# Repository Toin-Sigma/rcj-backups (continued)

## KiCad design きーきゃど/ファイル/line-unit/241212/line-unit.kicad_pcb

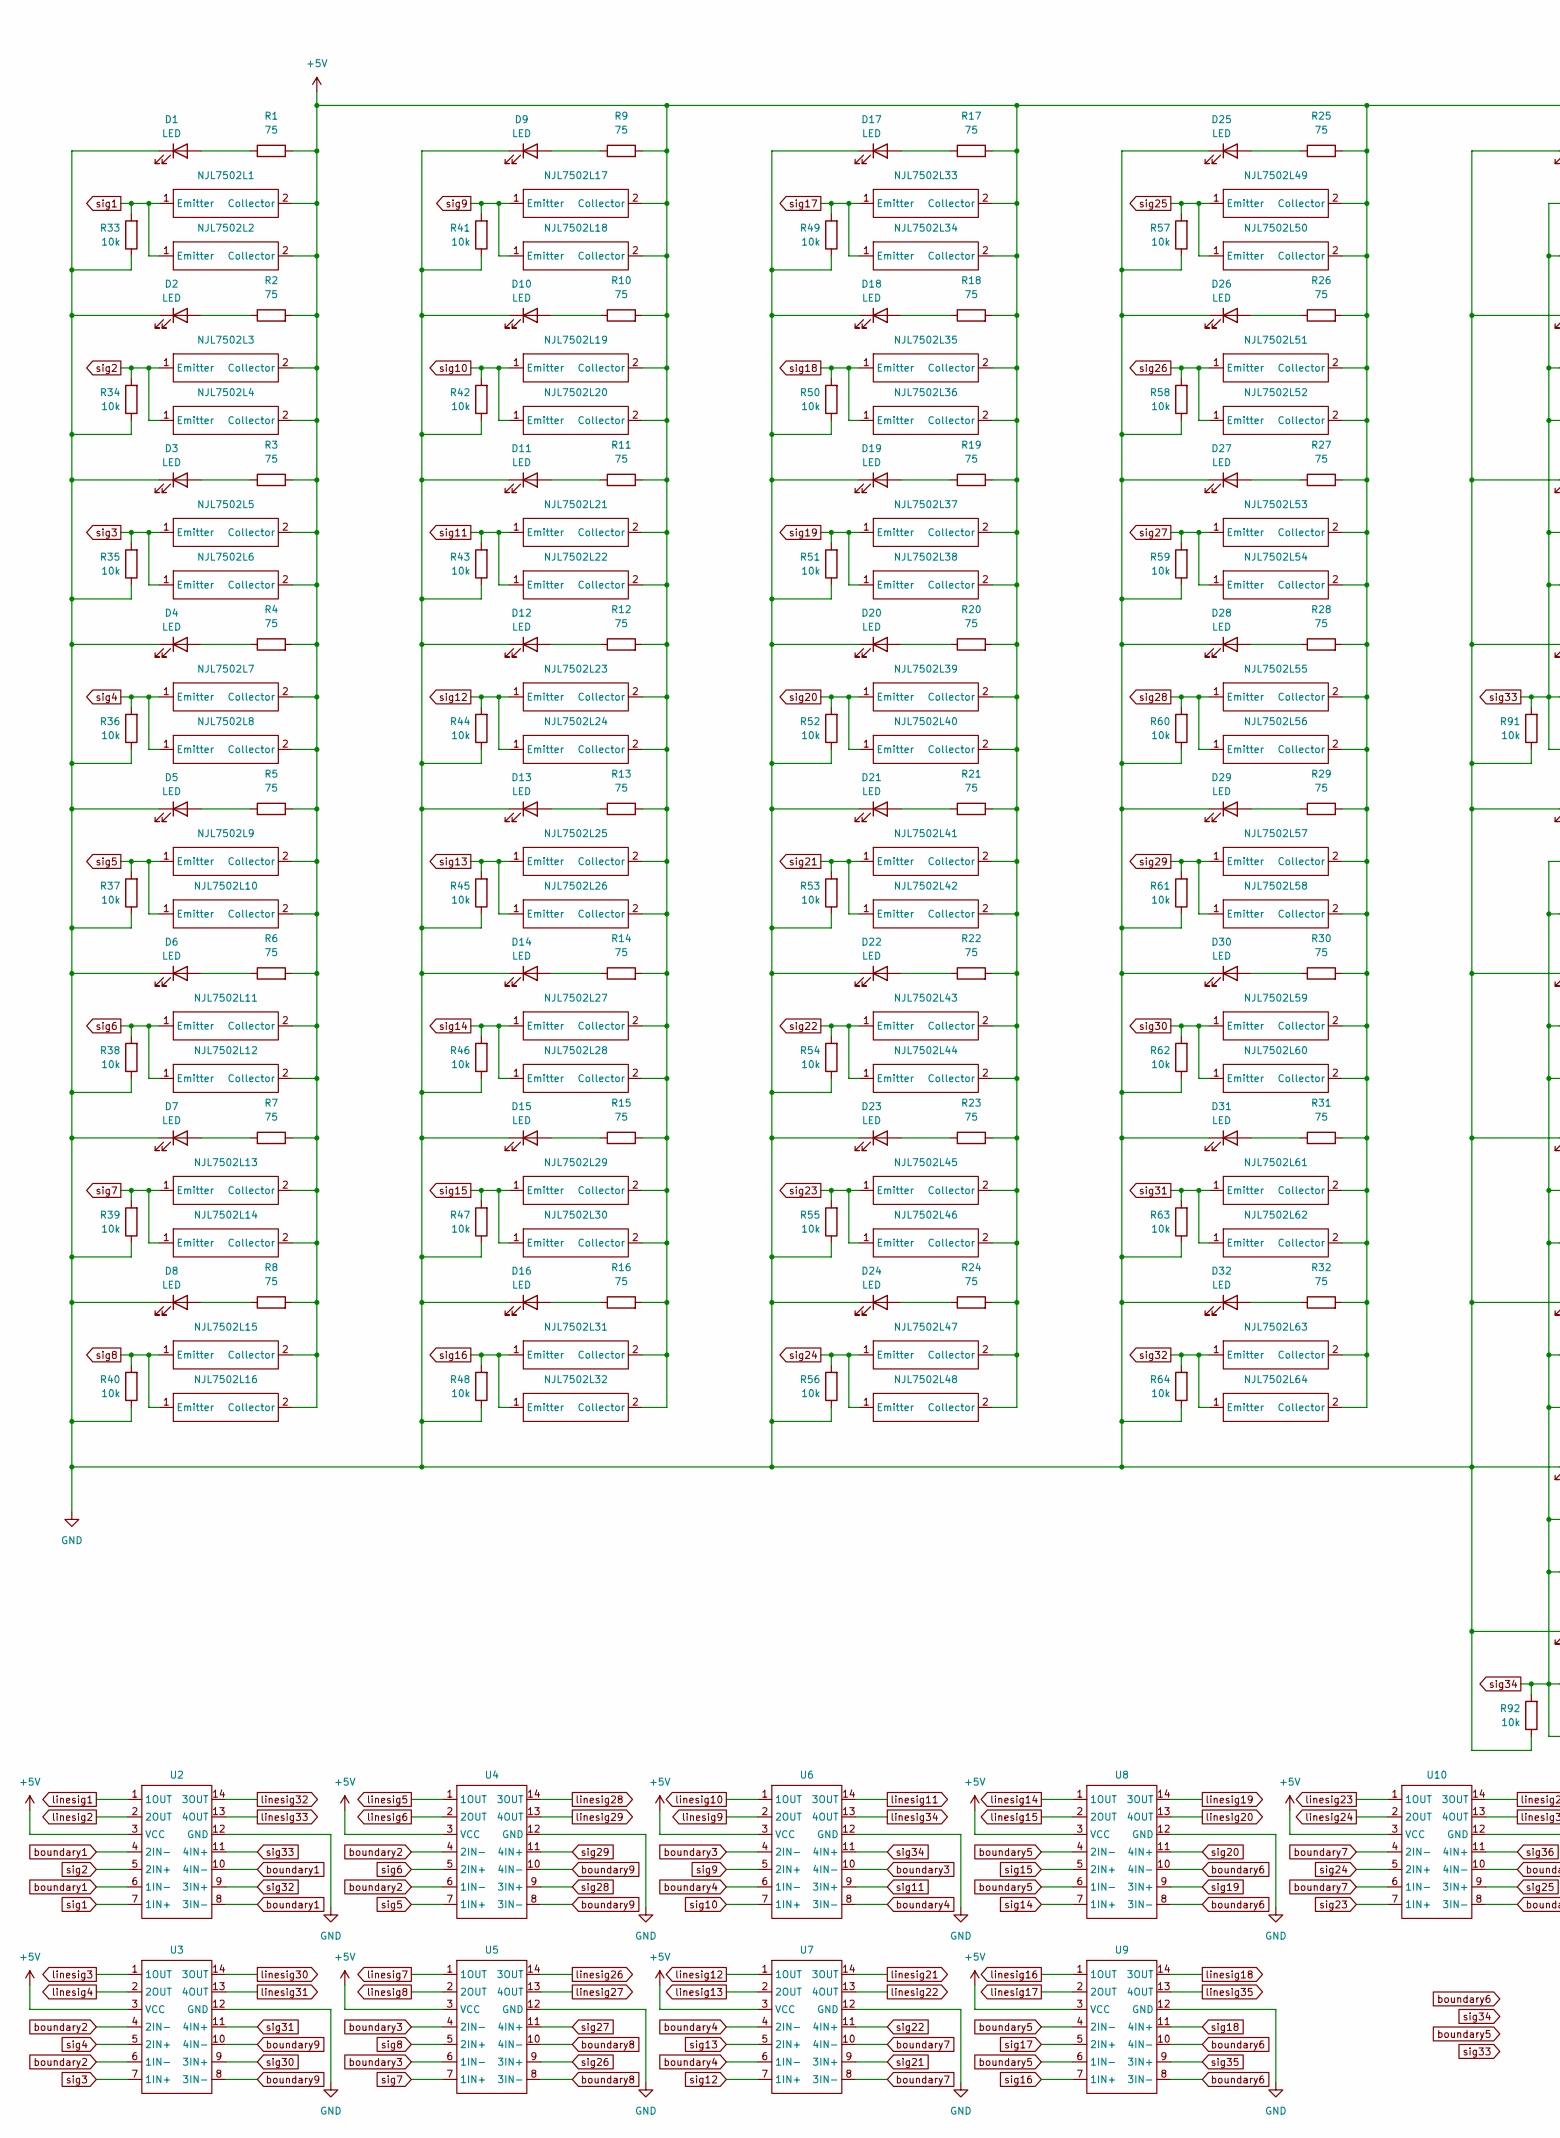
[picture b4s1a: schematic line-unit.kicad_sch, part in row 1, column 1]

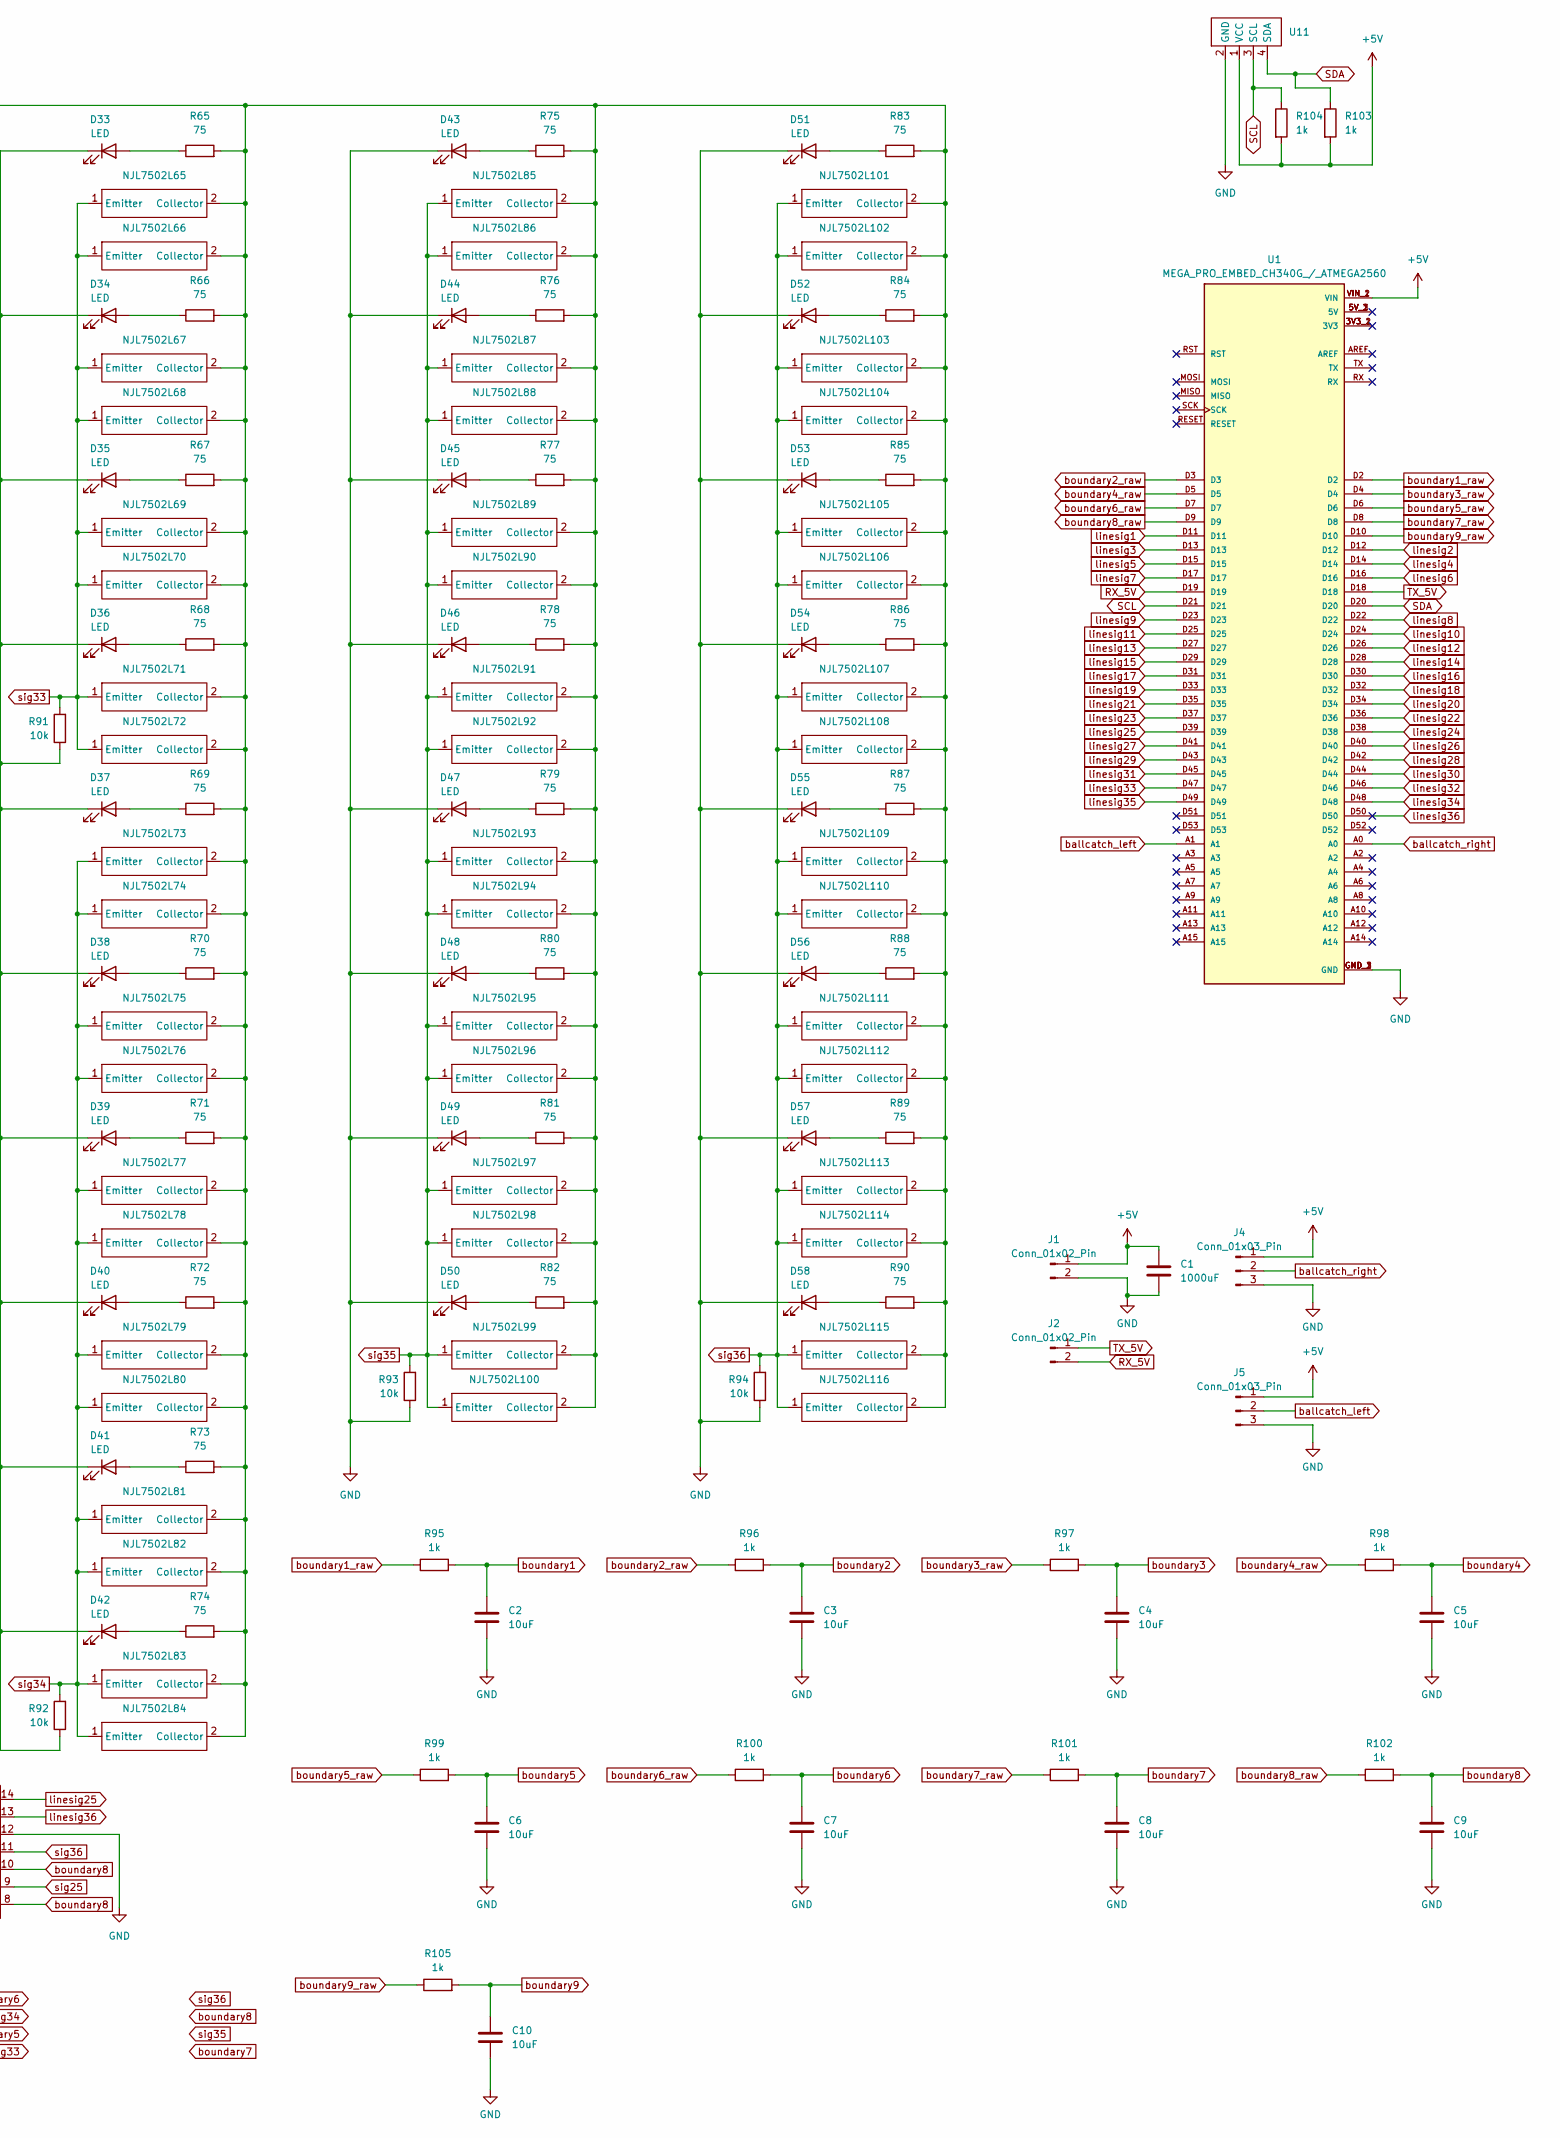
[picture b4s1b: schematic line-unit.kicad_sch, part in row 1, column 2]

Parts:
C1: 1000uF; CP_Radial_D12.5mm_P5.00mm
C2, C3, C4, C5, C6, C7, C8, C9, C10: 10uF; C-1206_3216-Handsolder
D1, D2, D3, D4, D5, D6, D7, D8, D9, D10, D11, D12, D13, D14, D15, D16, D17, D18, D19, D20, D21, D22, D23, D24, D25, D26, D27, D28, D29, D30, D31, D32, D33, D34, D35, D36, D37, D38, D39, D40, D41, D42, D43, D44, D45, D46, D47, D48, D49, D50, D51, D52, D53, D54, D55, D56, D57, D58: LED
J1: Conn_01x02_Pin; AMASS_XT30U-F_1x02_P5.0mm_Vertical
J2: Conn_01x02_Pin; JST_XH_B2B-XH-A_1x02_P2.50mm_Vertical
J4, J5: Conn_01x03_Pin; JST_XH_B3B-XH-A_1x03_P2.50mm_Vertical
NJL7502L1, NJL7502L2, NJL7502L3, NJL7502L4, NJL7502L5, NJL7502L6, NJL7502L7, NJL7502L8, NJL7502L9, NJL7502L10, NJL7502L11, NJL7502L12, NJL7502L13, NJL7502L14, NJL7502L15, NJL7502L16, NJL7502L17, NJL7502L18, NJL7502L19, NJL7502L20, NJL7502L21, NJL7502L22, NJL7502L23, NJL7502L24, NJL7502L25, NJL7502L26, NJL7502L27, NJL7502L28, NJL7502L29, NJL7502L30, NJL7502L31, NJL7502L32, NJL7502L33, NJL7502L34, NJL7502L35, NJL7502L36, NJL7502L37, NJL7502L38, NJL7502L39, NJL7502L40, NJL7502L41, NJL7502L42, NJL7502L43, NJL7502L44, NJL7502L45, NJL7502L46, NJL7502L47, NJL7502L48, NJL7502L49, NJL7502L50, NJL7502L51, NJL7502L52, NJL7502L53, NJL7502L54, NJL7502L55, NJL7502L56, NJL7502L57, NJL7502L58, NJL7502L59, NJL7502L60, NJL7502L61, NJL7502L62, NJL7502L63, NJL7502L64, NJL7502L65, NJL7502L66, NJL7502L67, NJL7502L68, NJL7502L69, NJL7502L70, NJL7502L71, NJL7502L72, NJL7502L73, NJL7502L74, NJL7502L75, NJL7502L76, NJL7502L77, NJL7502L78, NJL7502L79, NJL7502L80, NJL7502L81, NJL7502L82, NJL7502L83, NJL7502L84, NJL7502L85, NJL7502L86, NJL7502L87, NJL7502L88, NJL7502L89, NJL7502L90, NJL7502L91, NJL7502L92, NJL7502L93, NJL7502L94, NJL7502L95, NJL7502L96, NJL7502L97, NJL7502L98, NJL7502L99, NJL7502L100, NJL7502L101, NJL7502L102, NJL7502L103, NJL7502L104, NJL7502L105, NJL7502L106, NJL7502L107, NJL7502L108, NJL7502L109, NJL7502L110, NJL7502L111, NJL7502L112, NJL7502L113, NJL7502L114, NJL7502L115, NJL7502L116: NJL7502L
R1, R2, R3, R4, R5, R6, R7, R8, R9, R10, R11, R12, R13, R14, R15, R16, R17, R18, R19, R20, R21, R22, R23, R24, R25, R26, R27, R28, R29, R30, R31, R32, R65, R66, R67, R68, R69, R70, R71, R72, R73, R74, R75, R76, R77, R78, R79, R80, R81, R82, R83, R84, R85, R86, R87, R88, R89, R90: 75; R-1206_3216-Handsolder
R33, R34, R35, R36, R37, R38, R39, R40, R41, R42, R43, R44, R45, R46, R47, R48, R49, R50, R51, R52, R53, R54, R55, R56, R57, R58, R59, R60, R61, R62, R63, R64, R91, R92, R93, R94: 10k; R-1206_3216-Handsolder
R95, R96, R97, R98, R99, R100, R101, R102, R105: 1k; R-1206_3216-Handsolder
R103, R104: 1k
U1: MEGA_PRO_EMBED_CH340G_/_ATMEGA2560; MODULE_MEGA_PRO_EMBED_CH340G___ATMEGA2560
U2, U3, U4, U5, U6, U7, U8, U9, U10: LM339
U11: (no value)

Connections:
+5V: C1.1, J1.1, J4.1, J5.1, NJL7502L1.2 (Collector), NJL7502L2.2 (Collector), NJL7502L3.2 (Collector), NJL7502L4.2 (Collector), NJL7502L5.2 (Collector), NJL7502L6.2 (Collector), NJL7502L7.2 (Collector), NJL7502L8.2 (Collector), NJL7502L9.2 (Collector), NJL7502L10.2 (Collector), NJL7502L11.2 (Collector), NJL7502L12.2 (Collector), NJL7502L13.2 (Collector), NJL7502L14.2 (Collector), NJL7502L15.2 (Collector), NJL7502L16.2 (Collector), NJL7502L17.2 (Collector), NJL7502L18.2 (Collector), NJL7502L19.2 (Collector), NJL7502L20.2 (Collector), NJL7502L21.2 (Collector), NJL7502L22.2 (Collector), NJL7502L23.2 (Collector), NJL7502L24.2 (Collector), NJL7502L25.2 (Collector), NJL7502L26.2 (Collector), NJL7502L27.2 (Collector), NJL7502L28.2 (Collector), NJL7502L29.2 (Collector), NJL7502L30.2 (Collector), NJL7502L31.2 (Collector), NJL7502L32.2 (Collector), NJL7502L33.2 (Collector), NJL7502L34.2 (Collector), NJL7502L35.2 (Collector), NJL7502L36.2 (Collector), NJL7502L37.2 (Collector), NJL7502L38.2 (Collector), NJL7502L39.2 (Collector), NJL7502L40.2 (Collector), NJL7502L41.2 (Collector), NJL7502L42.2 (Collector), NJL7502L43.2 (Collector), NJL7502L44.2 (Collector), NJL7502L45.2 (Collector), NJL7502L46.2 (Collector), NJL7502L47.2 (Collector), NJL7502L48.2 (Collector), NJL7502L49.2 (Collector), NJL7502L50.2 (Collector), NJL7502L51.2 (Collector), NJL7502L52.2 (Collector), NJL7502L53.2 (Collector), NJL7502L54.2 (Collector), NJL7502L55.2 (Collector), NJL7502L56.2 (Collector), NJL7502L57.2 (Collector), NJL7502L58.2 (Collector), NJL7502L59.2 (Collector), NJL7502L60.2 (Collector), NJL7502L61.2 (Collector), NJL7502L62.2 (Collector), NJL7502L63.2 (Collector), NJL7502L64.2 (Collector), NJL7502L65.2 (Collector), NJL7502L66.2 (Collector), NJL7502L67.2 (Collector), NJL7502L68.2 (Collector), NJL7502L69.2 (Collector), NJL7502L70.2 (Collector), NJL7502L71.2 (Collector), NJL7502L72.2 (Collector), NJL7502L73.2 (Collector), NJL7502L74.2 (Collector), NJL7502L75.2 (Collector), NJL7502L76.2 (Collector), NJL7502L77.2 (Collector), NJL7502L78.2 (Collector), NJL7502L79.2 (Collector), NJL7502L80.2 (Collector), NJL7502L81.2 (Collector), NJL7502L82.2 (Collector), NJL7502L83.2 (Collector), NJL7502L84.2 (Collector), NJL7502L85.2 (Collector), NJL7502L86.2 (Collector), NJL7502L87.2 (Collector), NJL7502L88.2 (Collector), NJL7502L89.2 (Collector), NJL7502L90.2 (Collector), NJL7502L91.2 (Collector), NJL7502L92.2 (Collector), NJL7502L93.2 (Collector), NJL7502L94.2 (Collector), NJL7502L95.2 (Collector), NJL7502L96.2 (Collector), NJL7502L97.2 (Collector), NJL7502L98.2 (Collector), NJL7502L99.2 (Collector), NJL7502L100.2 (Collector), NJL7502L101.2 (Collector), NJL7502L102.2 (Collector), NJL7502L103.2 (Collector), NJL7502L104.2 (Collector), NJL7502L105.2 (Collector), NJL7502L106.2 (Collector), NJL7502L107.2 (Collector), NJL7502L108.2 (Collector), NJL7502L109.2 (Collector), NJL7502L110.2 (Collector), NJL7502L111.2 (Collector), NJL7502L112.2 (Collector), NJL7502L113.2 (Collector), NJL7502L114.2 (Collector), NJL7502L115.2 (Collector), NJL7502L116.2 (Collector), R1.2, R2.2, R3.2, R4.2, R5.2, R6.2, R7.2, R8.2, R9.2, R10.2, R11.2, R12.2, R13.2, R14.2, R15.2, R16.2, R17.2, R18.2, R19.2, R20.2, R21.2, R22.2, R23.2, R24.2, R25.2, R26.2, R27.2, R28.2, R29.2, R30.2, R31.2, R32.2, R65.2, R66.2, R67.2, R68.2, R69.2, R70.2, R71.2, R72.2, R73.2, R74.2, R75.2, R76.2, R77.2, R78.2, R79.2, R80.2, R81.2, R82.2, R83.2, R84.2, R85.2, R86.2, R87.2, R88.2, R89.2, R90.2, R103.2, R104.2, U1.VIN_1 (VIN), U1.VIN_2 (VIN), U2.3 (VCC), U3.3 (VCC), U4.3 (VCC), U5.3 (VCC), U6.3 (VCC), U7.3 (VCC), U8.3 (VCC), U9.3 (VCC), U10.3 (VCC), U11.1 (VCC)
GND: C1.2, C2.2, C3.2, C4.2, C5.2, C6.2, C7.2, C8.2, C9.2, C10.2, D1.1 (K), D2.1 (K), D3.1 (K), D4.1 (K), D5.1 (K), D6.1 (K), D7.1 (K), D8.1 (K), D9.1 (K), D10.1 (K), D11.1 (K), D12.1 (K), D13.1 (K), D14.1 (K), D15.1 (K), D16.1 (K), D17.1 (K), D18.1 (K), D19.1 (K), D20.1 (K), D21.1 (K), D22.1 (K), D23.1 (K), D24.1 (K), D25.1 (K), D26.1 (K), D27.1 (K), D28.1 (K), D29.1 (K), D30.1 (K), D31.1 (K), D32.1 (K), D33.1 (K), D34.1 (K), D35.1 (K), D36.1 (K), D37.1 (K), D38.1 (K), D39.1 (K), D40.1 (K), D41.1 (K), D42.1 (K), D43.1 (K), D44.1 (K), D45.1 (K), D46.1 (K), D47.1 (K), D48.1 (K), D49.1 (K), D50.1 (K), D51.1 (K), D52.1 (K), D53.1 (K), D54.1 (K), D55.1 (K), D56.1 (K), D57.1 (K), D58.1 (K), J1.2, J4.3, J5.3, R33.1, R34.1, R35.1, R36.1, R37.1, R38.1, R39.1, R40.1, R41.1, R42.1, R43.1, R44.1, R45.1, R46.1, R47.1, R48.1, R49.1, R50.1, R51.1, R52.1, R53.1, R54.1, R55.1, R56.1, R57.1, R58.1, R59.1, R60.1, R61.1, R62.1, R63.1, R64.1, R91.1, R92.1, R93.1, R94.1, U1.GND_1 (GND), U1.GND_2 (GND), U1.GND_3 (GND), U2.12 (GND), U3.12 (GND), U4.12 (GND), U5.12 (GND), U6.12 (GND), U7.12 (GND), U8.12 (GND), U9.12 (GND), U10.12 (GND), U11.2 (GND)
unnamed: D1.2 (A), R1.1
unnamed: D2.2 (A), R2.1
unnamed: D3.2 (A), R3.1
unnamed: D4.2 (A), R4.1
unnamed: D5.2 (A), R5.1
unnamed: D6.2 (A), R6.1
unnamed: D7.2 (A), R7.1
unnamed: D8.2 (A), R8.1
unnamed: D9.2 (A), R9.1
unnamed: D10.2 (A), R10.1
unnamed: D11.2 (A), R11.1
unnamed: D12.2 (A), R12.1
unnamed: D13.2 (A), R13.1
unnamed: D14.2 (A), R14.1
unnamed: D15.2 (A), R15.1
unnamed: D16.2 (A), R16.1
unnamed: D17.2 (A), R17.1
unnamed: D18.2 (A), R18.1
unnamed: D19.2 (A), R19.1
unnamed: D20.2 (A), R20.1
unnamed: D21.2 (A), R21.1
unnamed: D22.2 (A), R22.1
unnamed: D23.2 (A), R23.1
unnamed: D24.2 (A), R24.1
unnamed: D25.2 (A), R25.1
unnamed: D26.2 (A), R26.1
unnamed: D27.2 (A), R27.1
unnamed: D28.2 (A), R28.1
unnamed: D29.2 (A), R29.1
unnamed: D30.2 (A), R30.1
unnamed: D31.2 (A), R31.1
unnamed: D32.2 (A), R32.1
unnamed: D33.2 (A), R65.1
unnamed: D34.2 (A), R66.1
unnamed: D35.2 (A), R67.1
unnamed: D36.2 (A), R68.1
unnamed: D37.2 (A), R69.1
unnamed: D38.2 (A), R70.1
unnamed: D39.2 (A), R71.1
unnamed: D40.2 (A), R72.1
unnamed: D41.2 (A), R73.1
unnamed: D42.2 (A), R74.1
unnamed: D43.2 (A), R75.1
unnamed: D44.2 (A), R76.1
unnamed: D45.2 (A), R77.1
unnamed: D46.2 (A), R78.1
unnamed: D47.2 (A), R79.1
unnamed: D48.2 (A), R80.1
unnamed: D49.2 (A), R81.1
unnamed: D50.2 (A), R82.1
unnamed: D51.2 (A), R83.1
unnamed: D52.2 (A), R84.1
unnamed: D53.2 (A), R85.1
unnamed: D54.2 (A), R86.1
unnamed: D55.2 (A), R87.1
unnamed: D56.2 (A), R88.1
unnamed: D57.2 (A), R89.1
unnamed: D58.2 (A), R90.1
RX_5V: J2.2, U1.D19
SCL: R104.1, U1.D21, U11.3 (SCL)
SDA: R103.1, U1.D20, U11.4 (SDA)
TX_5V: J2.1, U1.D18
ballcatch_left: J5.2, U1.A1
ballcatch_right: J4.2, U1.A0
boundary1: C2.1, R95.2, U2.4 (2IN-), U2.6 (1IN-), U2.8 (3IN-), U2.10 (4IN-)
boundary1_raw: R95.1, U1.D2
boundary2: C3.1, R96.2, U3.4 (2IN-), U3.6 (1IN-), U4.4 (2IN-), U4.6 (1IN-)
boundary2_raw: R96.1, U1.D3
boundary3: C4.1, R97.2, U5.4 (2IN-), U5.6 (1IN-), U6.4 (2IN-), U6.10 (4IN-)
boundary3_raw: R97.1, U1.D4
boundary4: C5.1, R98.2, U6.6 (1IN-), U6.8 (3IN-), U7.4 (2IN-), U7.6 (1IN-)
boundary4_raw: R98.1, U1.D5
boundary5: C6.1, R99.2, U8.4 (2IN-), U8.6 (1IN-), U9.4 (2IN-), U9.6 (1IN-)
boundary5_raw: R99.1, U1.D6
boundary6: C7.1, R100.2, U8.8 (3IN-), U8.10 (4IN-), U9.8 (3IN-), U9.10 (4IN-)
boundary6_raw: R100.1, U1.D7
boundary7: C8.1, R101.2, U7.8 (3IN-), U7.10 (4IN-), U10.4 (2IN-), U10.6 (1IN-)
boundary7_raw: R101.1, U1.D8
boundary8: C9.1, R102.2, U5.8 (3IN-), U5.10 (4IN-), U10.8 (3IN-), U10.10 (4IN-)
boundary8_raw: R102.1, U1.D9
boundary9: C10.1, R105.2, U3.8 (3IN-), U3.10 (4IN-), U4.8 (3IN-), U4.10 (4IN-)
boundary9_raw: R105.1, U1.D10
linesig1: U1.D11, U2.1 (1OUT)
linesig2: U1.D12, U2.2 (2OUT)
linesig3: U1.D13, U3.1 (1OUT)
linesig4: U1.D14, U3.2 (2OUT)
linesig5: U1.D15, U4.1 (1OUT)
linesig6: U1.D16, U4.2 (2OUT)
linesig7: U1.D17, U5.1 (1OUT)
linesig8: U1.D22, U5.2 (2OUT)
linesig9: U1.D23, U6.2 (2OUT)
linesig10: U1.D24, U6.1 (1OUT)
linesig11: U1.D25, U6.14 (3OUT)
linesig12: U1.D26, U7.1 (1OUT)
linesig13: U1.D27, U7.2 (2OUT)
linesig14: U1.D28, U8.1 (1OUT)
linesig15: U1.D29, U8.2 (2OUT)
linesig16: U1.D30, U9.1 (1OUT)
linesig17: U1.D31, U9.2 (2OUT)
linesig18: U1.D32, U9.14 (3OUT)
linesig19: U1.D33, U8.14 (3OUT)
linesig20: U1.D34, U8.13 (4OUT)
linesig21: U1.D35, U7.14 (3OUT)
linesig22: U1.D36, U7.13 (4OUT)
linesig23: U1.D37, U10.1 (1OUT)
linesig24: U1.D38, U10.2 (2OUT)
linesig25: U1.D39, U10.14 (3OUT)
linesig26: U1.D40, U5.14 (3OUT)
linesig27: U1.D41, U5.13 (4OUT)
linesig28: U1.D42, U4.14 (3OUT)
linesig29: U1.D43, U4.13 (4OUT)
linesig30: U1.D44, U3.14 (3OUT)
linesig31: U1.D45, U3.13 (4OUT)
linesig32: U1.D46, U2.14 (3OUT)
linesig33: U1.D47, U2.13 (4OUT)
linesig34: U1.D48, U6.13 (4OUT)
linesig35: U1.D49, U9.13 (4OUT)
linesig36: U1.D50, U10.13 (4OUT)
sig1: NJL7502L1.1 (Emitter), NJL7502L2.1 (Emitter), R33.2, U2.7 (1IN+)
sig2: NJL7502L3.1 (Emitter), NJL7502L4.1 (Emitter), R34.2, U2.5 (2IN+)
sig3: NJL7502L5.1 (Emitter), NJL7502L6.1 (Emitter), R35.2, U3.7 (1IN+)
sig4: NJL7502L7.1 (Emitter), NJL7502L8.1 (Emitter), R36.2, U3.5 (2IN+)
sig5: NJL7502L9.1 (Emitter), NJL7502L10.1 (Emitter), R37.2, U4.7 (1IN+)
sig6: NJL7502L11.1 (Emitter), NJL7502L12.1 (Emitter), R38.2, U4.5 (2IN+)
sig7: NJL7502L13.1 (Emitter), NJL7502L14.1 (Emitter), R39.2, U5.7 (1IN+)
sig8: NJL7502L15.1 (Emitter), NJL7502L16.1 (Emitter), R40.2, U5.5 (2IN+)
sig9: NJL7502L17.1 (Emitter), NJL7502L18.1 (Emitter), R41.2, U6.5 (2IN+)
sig10: NJL7502L19.1 (Emitter), NJL7502L20.1 (Emitter), R42.2, U6.7 (1IN+)
sig11: NJL7502L21.1 (Emitter), NJL7502L22.1 (Emitter), R43.2, U6.9 (3IN+)
sig12: NJL7502L23.1 (Emitter), NJL7502L24.1 (Emitter), R44.2, U7.7 (1IN+)
sig13: NJL7502L25.1 (Emitter), NJL7502L26.1 (Emitter), R45.2, U7.5 (2IN+)
sig14: NJL7502L27.1 (Emitter), NJL7502L28.1 (Emitter), R46.2, U8.7 (1IN+)
sig15: NJL7502L29.1 (Emitter), NJL7502L30.1 (Emitter), R47.2, U8.5 (2IN+)
sig16: NJL7502L31.1 (Emitter), NJL7502L32.1 (Emitter), R48.2, U9.7 (1IN+)
sig17: NJL7502L33.1 (Emitter), NJL7502L34.1 (Emitter), R49.2, U9.5 (2IN+)
sig18: NJL7502L35.1 (Emitter), NJL7502L36.1 (Emitter), R50.2, U9.11 (4IN+)
sig19: NJL7502L37.1 (Emitter), NJL7502L38.1 (Emitter), R51.2, U8.9 (3IN+)
sig20: NJL7502L39.1 (Emitter), NJL7502L40.1 (Emitter), R52.2, U8.11 (4IN+)
sig21: NJL7502L41.1 (Emitter), NJL7502L42.1 (Emitter), R53.2, U7.9 (3IN+)
sig22: NJL7502L43.1 (Emitter), NJL7502L44.1 (Emitter), R54.2, U7.11 (4IN+)
sig23: NJL7502L45.1 (Emitter), NJL7502L46.1 (Emitter), R55.2, U10.7 (1IN+)
sig24: NJL7502L47.1 (Emitter), NJL7502L48.1 (Emitter), R56.2, U10.5 (2IN+)
sig25: NJL7502L49.1 (Emitter), NJL7502L50.1 (Emitter), R57.2, U10.9 (3IN+)
sig26: NJL7502L51.1 (Emitter), NJL7502L52.1 (Emitter), R58.2, U5.9 (3IN+)
sig27: NJL7502L53.1 (Emitter), NJL7502L54.1 (Emitter), R59.2, U5.11 (4IN+)
sig28: NJL7502L55.1 (Emitter), NJL7502L56.1 (Emitter), R60.2, U4.9 (3IN+)
sig29: NJL7502L57.1 (Emitter), NJL7502L58.1 (Emitter), R61.2, U4.11 (4IN+)
sig30: NJL7502L59.1 (Emitter), NJL7502L60.1 (Emitter), R62.2, U3.9 (3IN+)
sig31: NJL7502L61.1 (Emitter), NJL7502L62.1 (Emitter), R63.2, U3.11 (4IN+)
sig32: NJL7502L63.1 (Emitter), NJL7502L64.1 (Emitter), R64.2, U2.9 (3IN+)
sig33: NJL7502L65.1 (Emitter), NJL7502L66.1 (Emitter), NJL7502L67.1 (Emitter), NJL7502L68.1 (Emitter), NJL7502L69.1 (Emitter), NJL7502L70.1 (Emitter), NJL7502L71.1 (Emitter), NJL7502L72.1 (Emitter), R91.2, U2.11 (4IN+)
sig34: NJL7502L73.1 (Emitter), NJL7502L74.1 (Emitter), NJL7502L75.1 (Emitter), NJL7502L76.1 (Emitter), NJL7502L77.1 (Emitter), NJL7502L78.1 (Emitter), NJL7502L79.1 (Emitter), NJL7502L80.1 (Emitter), NJL7502L81.1 (Emitter), NJL7502L82.1 (Emitter), NJL7502L83.1 (Emitter), NJL7502L84.1 (Emitter), R92.2, U6.11 (4IN+)
sig35: NJL7502L85.1 (Emitter), NJL7502L86.1 (Emitter), NJL7502L87.1 (Emitter), NJL7502L88.1 (Emitter), NJL7502L89.1 (Emitter), NJL7502L90.1 (Emitter), NJL7502L91.1 (Emitter), NJL7502L92.1 (Emitter), NJL7502L93.1 (Emitter), NJL7502L94.1 (Emitter), NJL7502L95.1 (Emitter), NJL7502L96.1 (Emitter), NJL7502L97.1 (Emitter), NJL7502L98.1 (Emitter), NJL7502L99.1 (Emitter), NJL7502L100.1 (Emitter), R93.2, U9.9 (3IN+)
sig36: NJL7502L101.1 (Emitter), NJL7502L102.1 (Emitter), NJL7502L103.1 (Emitter), NJL7502L104.1 (Emitter), NJL7502L105.1 (Emitter), NJL7502L106.1 (Emitter), NJL7502L107.1 (Emitter), NJL7502L108.1 (Emitter), NJL7502L109.1 (Emitter), NJL7502L110.1 (Emitter), NJL7502L111.1 (Emitter), NJL7502L112.1 (Emitter), NJL7502L113.1 (Emitter), NJL7502L114.1 (Emitter), NJL7502L115.1 (Emitter), NJL7502L116.1 (Emitter), R94.2, U10.11 (4IN+)

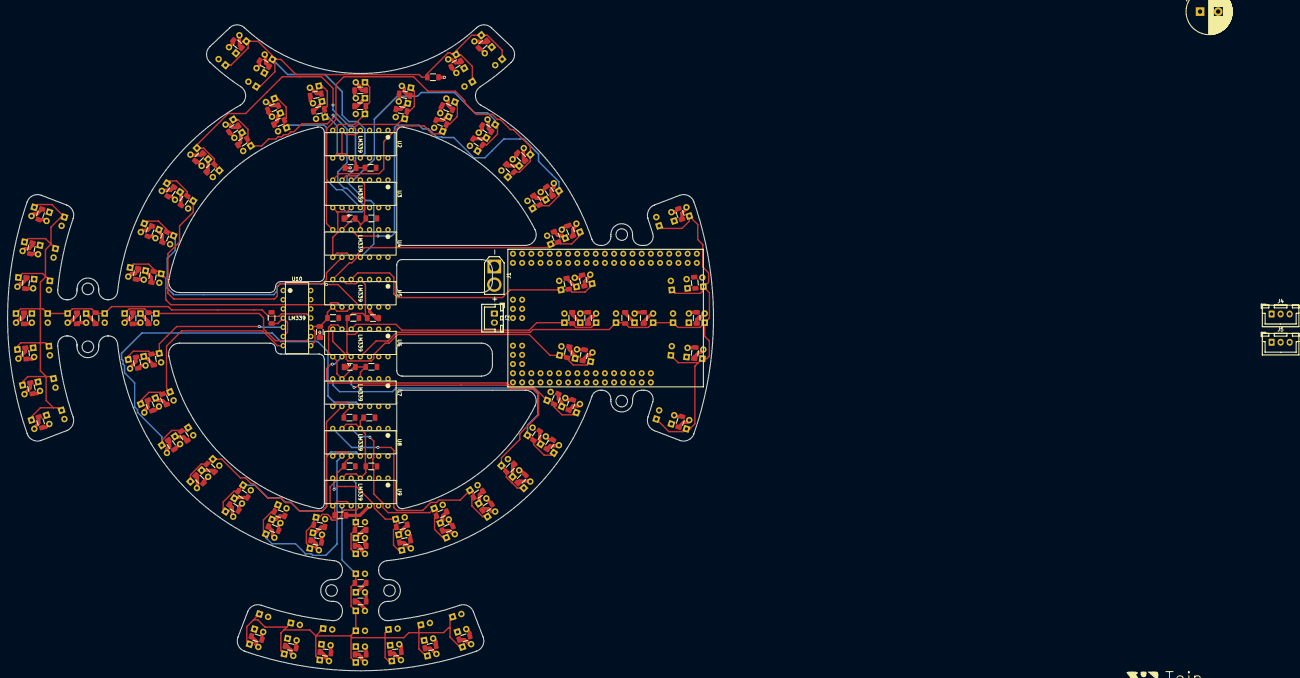
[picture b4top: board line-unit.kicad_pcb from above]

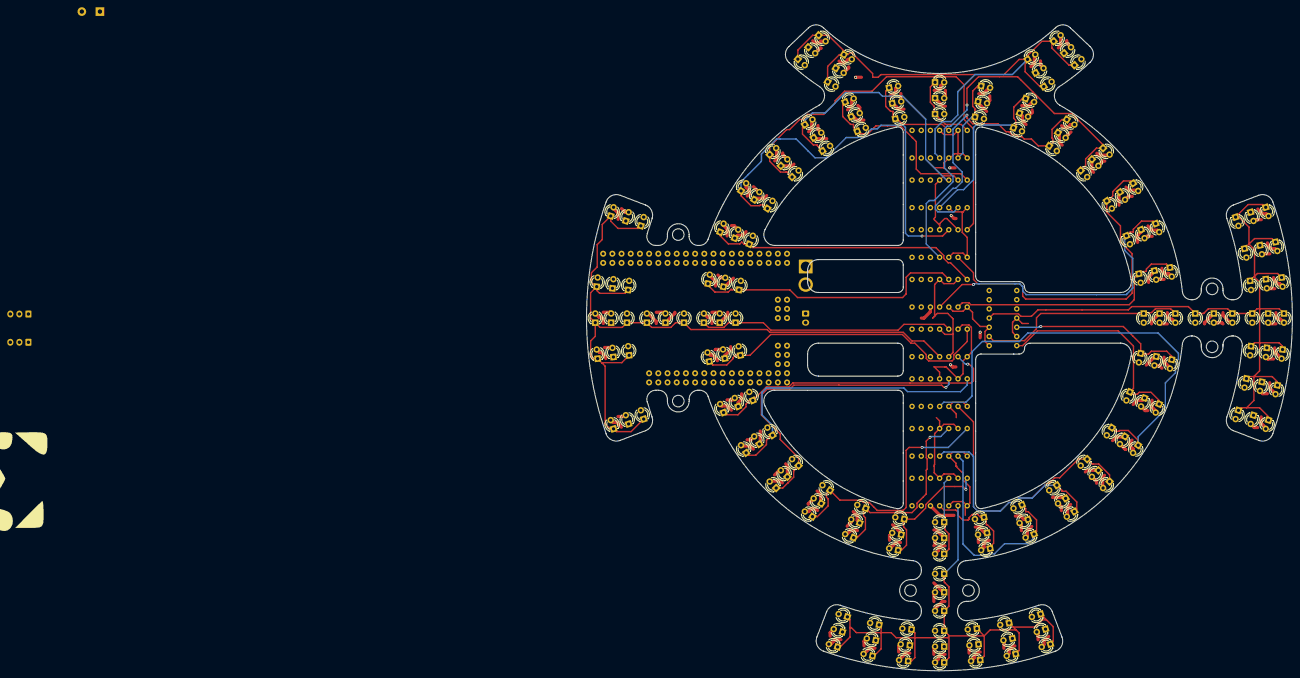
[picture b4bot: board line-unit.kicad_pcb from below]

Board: 4 copper layers, 195.0 x 178.4 mm, 299 parts (174 on the bottom side), 153 nets.

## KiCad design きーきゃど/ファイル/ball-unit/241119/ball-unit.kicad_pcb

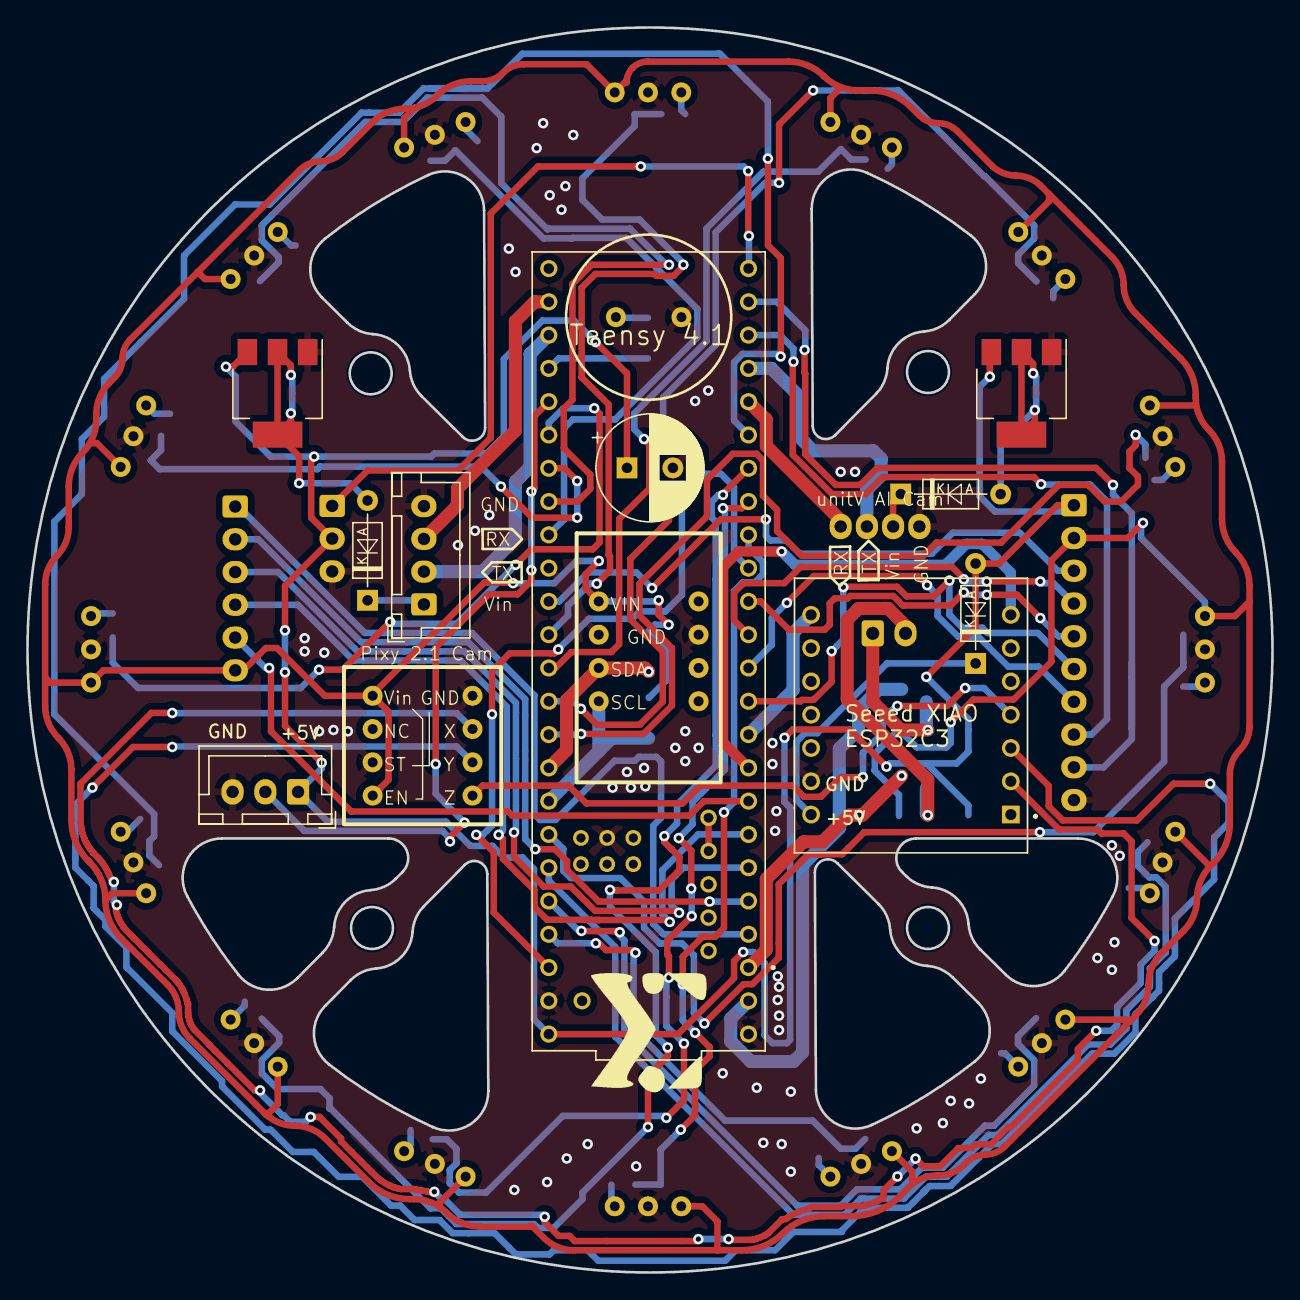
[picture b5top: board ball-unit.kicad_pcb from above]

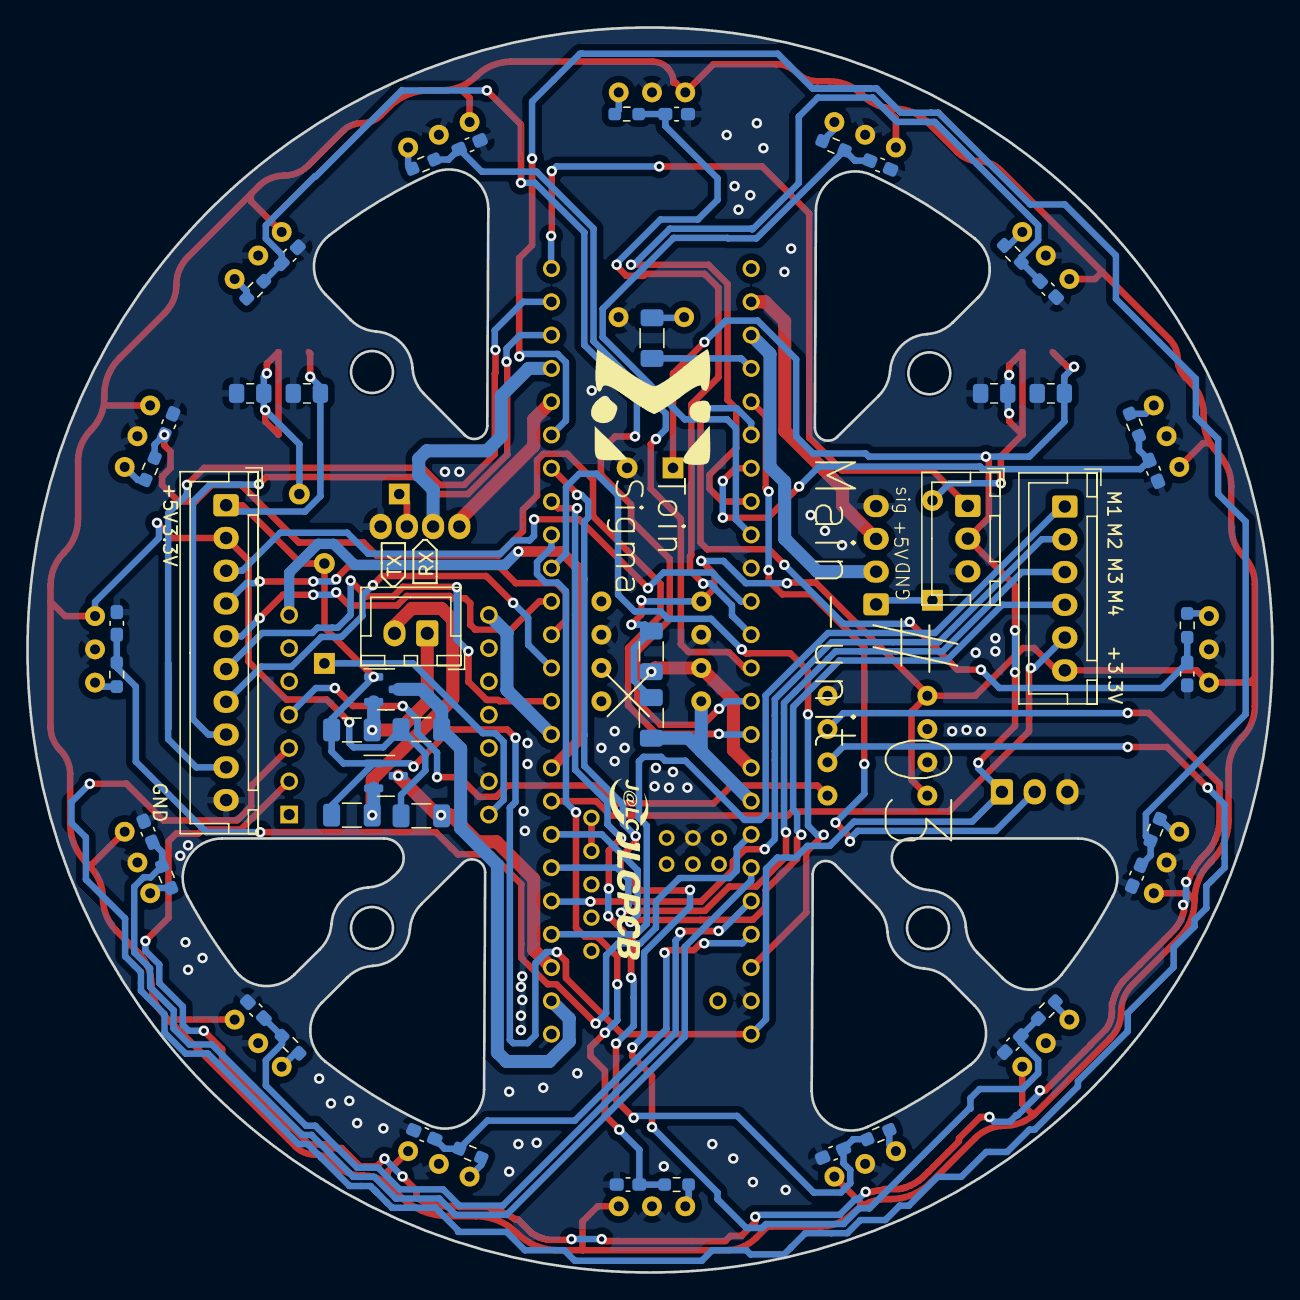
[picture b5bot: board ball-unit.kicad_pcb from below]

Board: 2 copper layers, 95.0 x 95.0 mm, 79 parts (65 on the bottom side), 71 nets.

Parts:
BZ1: Buzzer; PKM13EPYH4000-A0
C1, C2, C3, C4, C5, C6, C7, C8, C9, C10, C11, C12, C13, C14, C15, C16: 0.33μF; C_0603_1608Metric_Pad1.08x0.95mm_HandSolder
C17: 470uf; CP_Radial_D8.0mm_P3.50mm
C18, C19, C20, C21: 10uF; C_0805_2012Metric_Pad1.18x1.45mm_HandSolder
D1, D2, D3: D; BAT43
J1: Conn_01x10_Pin; JST_XH_B10B-XH-A_1x10_P2.50mm_Vertical
J2: Conn_01x02_Pin; JST_XH_B2B-XH-A_1x02_P2.50mm_Vertical
J3: Conn_01x06_Pin; JST_XH_B6B-XH-A_1x06_P2.50mm_Vertical
J4, J5: Conn_01x03_Pin; JST_XH_B3B-XH-A_1x03_P2.50mm_Vertical
J6: Conn_01x04_Pin; grove - 4
J7: Conn_01x04_Pin; UART - XH4
R1, R2, R3, R4, R5, R6, R7, R8, R9, R10, R11, R12, R13, R14, R15, R16: 39k; R_0603_1608Metric_Pad0.98x0.95mm_HandSolder
R17, R18, R19, R20: 10k; R_1206_3216Metric_Pad1.30x1.75mm_HandSolder
R21, R22, R23: 1k; R_1206_3216Metric_Pad1.30x1.75mm_HandSolder
U1, U2, U3, U4, U5, U6, U7, U8, U9, U10, U11, U12, U13, U14, U15, U16: tssp58038
U17: KXTC9-2050
U18: AE-BN0055-B0
U19: Teensy 4.1; teensy 4.1
U20: Seeed Studio XIAO ESP32C3
U21, U22: SOT-23
U23, U24: SOT-223-3_TabPin2

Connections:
+3.3V: J1.2, J3.6, R18.2, R20.2, R22.1, R23.1, U1.3 (VCC), U2.3 (VCC), U3.3 (VCC), U4.3 (VCC), U5.3 (VCC), U6.3 (VCC), U7.3 (VCC), U8.3 (VCC), U9.3 (VCC), U10.3 (VCC), U11.3 (VCC), U12.3 (VCC), U13.3 (VCC), U14.3 (VCC), U15.3 (VCC), U16.3 (VCC), U17.1 (3.3Vin), U17.4 (EN), U18.1 (VIN)
+5V: C17.1, C19.1, C21.1, D1.2 (A), J1.1, J4.1, J5.2, R17.2, R19.2, U19.VIN, U21.1 (Gate), U22.1 (Gate), U23.3 (VIN), U24.3 (VIN)
GND: BZ1.2 (+), C1.2, C2.2, C3.2, C4.2, C5.2, C6.2, C7.2, C8.2, C9.2, C10.2, C11.2, C12.2, C13.2, C14.2, C15.2, C16.2, C17.2, C18.1, C19.2, C20.1, C21.2, J1.10, J4.3, J5.3, J6.1, J7.4, U1.2 (GND), U2.2 (GND), U3.2 (GND), U4.2 (GND), U5.2 (GND), U6.2 (GND), U7.2 (GND), U8.2 (GND), U9.2 (GND), U10.2 (GND), U11.2 (GND), U12.2 (GND), U13.2 (GND), U14.2 (GND), U15.2 (GND), U16.2 (GND), U17.3 (ST), U17.5 (GND), U18.2 (GND), U18.7 (GND), U19.GND1 (GND), U19.GND2 (GND), U19.GND3 (GND), U19.GND5 (GND), U20.13 (GND), U23.1 (GND), U24.1 (GND)
Kick: J5.1, U19.32 (OUT1B)
M1: J3.1, U19.2 (OUT2)
M2: J3.2, U19.3 (LRCLK2)
M3: J3.3, U19.4 (BCLK2)
M4: J3.4, U19.5 (IN2)
NeopiSig: J4.2, U19.37 (CS3)
unnamed: BZ1.1 (-), R21.2
unnamed: D1.1 (K), U20.14 (VUSB)
unnamed: D2.1 (K), J6.2
unnamed: D3.1 (K), J7.1
unnamed: R1.2, U1.1 (OUT)
unnamed: R2.2, U2.1 (OUT)
unnamed: R3.2, U3.1 (OUT)
unnamed: R4.2, U4.1 (OUT)
unnamed: R5.2, U5.1 (OUT)
unnamed: R6.2, U6.1 (OUT)
unnamed: R7.2, U7.1 (OUT)
unnamed: R8.2, U8.1 (OUT)
unnamed: R9.2, U9.1 (OUT)
unnamed: R10.2, U10.1 (OUT)
unnamed: R11.2, U11.1 (OUT)
unnamed: R12.2, U12.1 (OUT)
unnamed: R13.2, U13.1 (OUT)
unnamed: R14.2, U14.1 (OUT)
unnamed: R15.2, U15.1 (OUT)
unnamed: R16.2, U16.1 (OUT)
Pixy-Vin: C20.2, D3.2 (A), U24.2 (OUT)
RX_5V: J2.2, R19.1, U22.2 (Source)
RX_ESP: U19.7 (RX2), U20.7 (TX_D6)
RX_Pixy: J7.3, U19.34 (RX8)
RX_UnitV: J6.4, U19.28 (RX7)
RX_line: R18.1, U19.0 (RX1), U21.3 (Drain)
SCL_gyro: R23.2, U18.4 (SCL), U19.19 (A5)
SDA_gyro: R22.2, U18.3 (SDA), U19.18 (A4)
TX_5V: J2.1, R17.1, U21.2 (Source)
TX_ESP: U19.8 (TX2), U20.8 (RX_D7)
TX_Pixy: J7.2, U19.35 (TX8)
TX_UnitV: J6.3, U19.29 (TX7)
TX_line: R20.1, U19.1 (TX1), U22.3 (Drain)
acce_x: U17.6 (X), U20.2 (D1)
acce_y: U17.7 (Y), U20.3 (D2)
acce_z: U17.8 (Z), U20.4 (D3)
at-gk: J1.4, U19.11 (MOSI)
buzzer: R21.1, U19.36 (CS2)
motor-start: J1.3, U19.13 (SCK)
neopixel: J1.6, U19.9 (OUT1C)
sig1: C1.1, R1.1, U19.14 (A0)
sig2: C2.1, R2.1, U19.15 (A1)
sig3: C3.1, R3.1, U19.16 (A2)
sig4: C4.1, R4.1, U19.17 (A3)
sig5: C5.1, R5.1, U19.20 (A6)
sig6: C6.1, R6.1, U19.21 (A7)
sig7: C7.1, R7.1, U19.22 (A8)
sig8: C8.1, R8.1, U19.23 (A9)
sig9: C9.1, R9.1, U19.24 (A10)
sig10: C10.1, R10.1, U19.25 (A11)
sig11: C11.1, R11.1, U19.26 (A12)
sig12: C12.1, R12.1, U19.27 (A13)
sig13: C13.1, R13.1, U19.38 (A14)
sig14: C14.1, R14.1, U19.39 (A15)
sig15: C15.1, R15.1, U19.40 (A16)
sig16: C16.1, R16.1, U19.41 (A17)
swA: J1.7, U19.10 (CS1)
swB: J1.8, U19.30 (CRX3)
swC: J1.9, U19.31 (CTX3)
to-MD: J3.5, U19.6 (OUT1D)
unitV-Vin: C18.2, D2.2 (A), U23.2 (OUT)
whichgoal: J1.5, U19.12 (MISO)
